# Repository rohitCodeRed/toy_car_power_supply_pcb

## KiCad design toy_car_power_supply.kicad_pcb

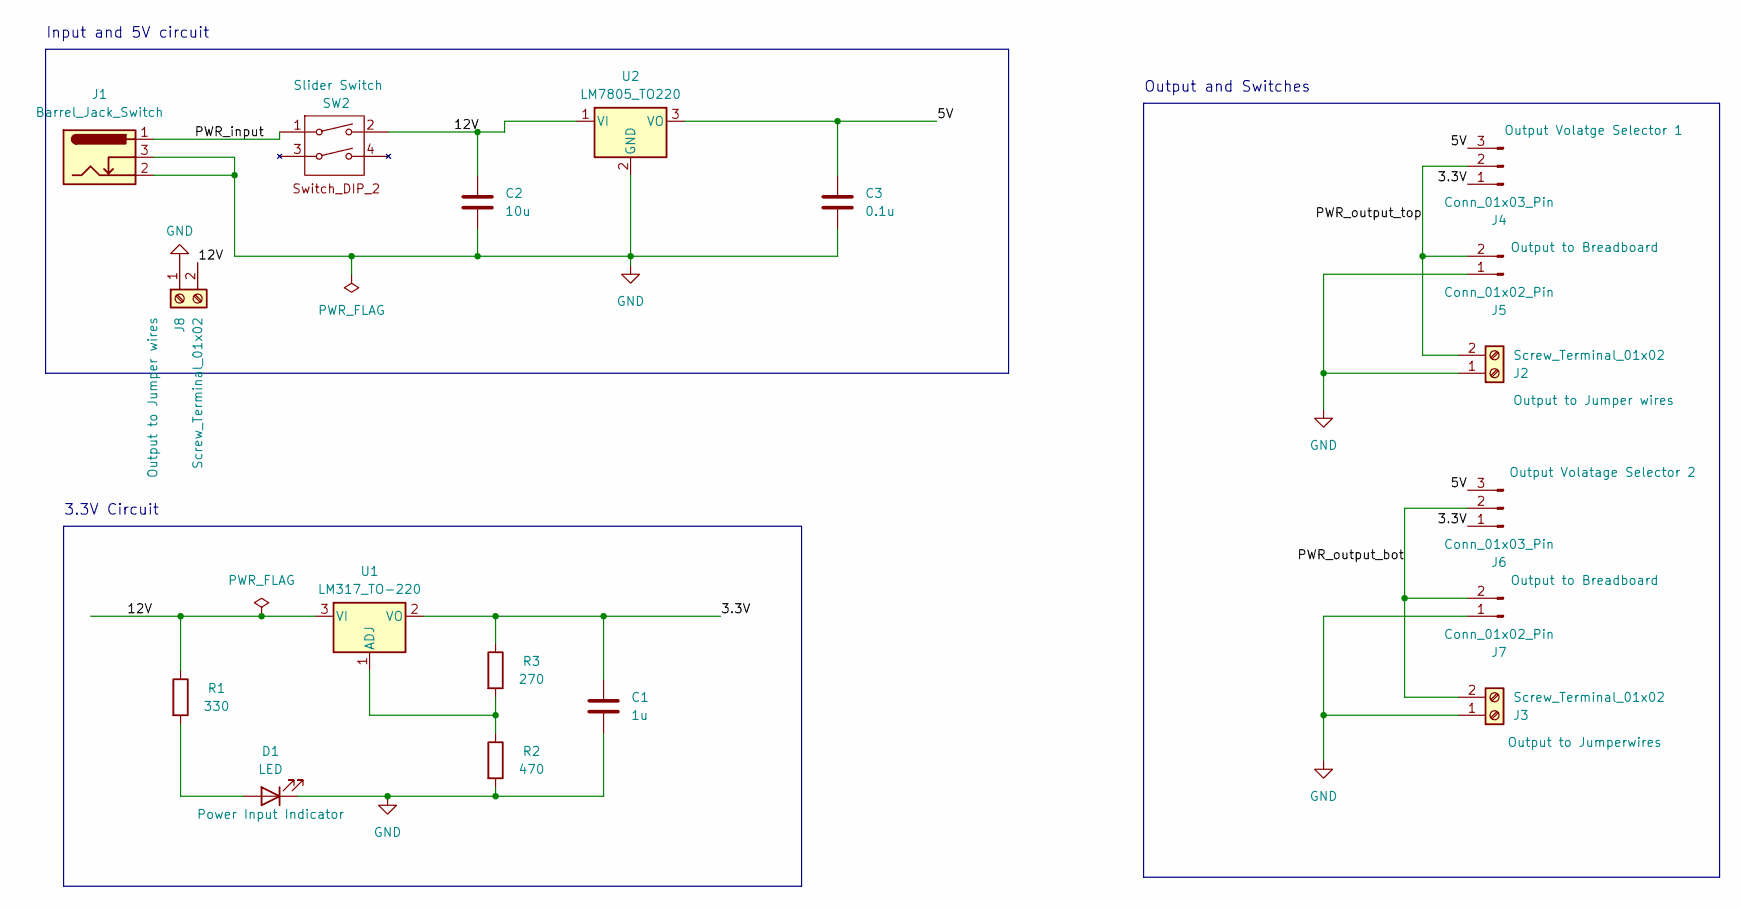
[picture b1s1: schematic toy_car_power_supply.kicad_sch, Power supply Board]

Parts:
C1: 1u; C_Disc_D3.0mm_W1.6mm_P2.50mm
C2: 10u; C_Disc_D3.0mm_W1.6mm_P2.50mm
C3: 0.1u; C_Disc_D3.0mm_W1.6mm_P2.50mm
D1: LED; LED_D5.0mm
J1: Barrel_Jack_Switch; BarrelJack_Horizontal
J2, J3, J8: Screw_Terminal_01x02; TerminalBlock_bornier-2_P5.08mm
J4, J6: Conn_01x03_Pin; PinHeader_1x03_P2.54mm_Vertical
J5, J7: Conn_01x02_Pin; PinHeader_1x02_P2.54mm_Vertical
R1: 330; R_Axial_DIN0204_L3.6mm_D1.6mm_P7.62mm_Horizontal
R2: 470; R_Axial_DIN0204_L3.6mm_D1.6mm_P7.62mm_Horizontal
R3: 270; R_Axial_DIN0204_L3.6mm_D1.6mm_P7.62mm_Horizontal
SW2: Slider Switch; DIP-4_W7.62mm
U1: LM317_TO-220; TO-220-3_Vertical
U2: LM7805_TO220; TO-220-3_Vertical

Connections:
/3.3V: C1.2, J4.1, J6.1, R3.1, U1.2 (VO)
/5V: C3.1, J4.3, J6.3, U2.3 (VO)
/12V: C2.1, J8.2, R1.1, SW2.2, U1.3 (VI), U2.1 (VI)
/PWR_input: J1.1, SW2.1
/PWR_output_bot: J3.2, J6.2, J7.2
/PWR_output_top: J2.2, J4.2, J5.2
GND: C1.1, C2.2, C3.2, D1.1 (K), J1.2, J1.3, J2.1, J3.1, J5.1, J7.1, J8.1, R2.2, U2.2 (GND)
unnamed: D1.2 (A), R1.2
unnamed: R2.1, R3.2, U1.1 (ADJ)

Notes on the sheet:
3.3V Circuit
Output and Switches
Input and 5V circuit

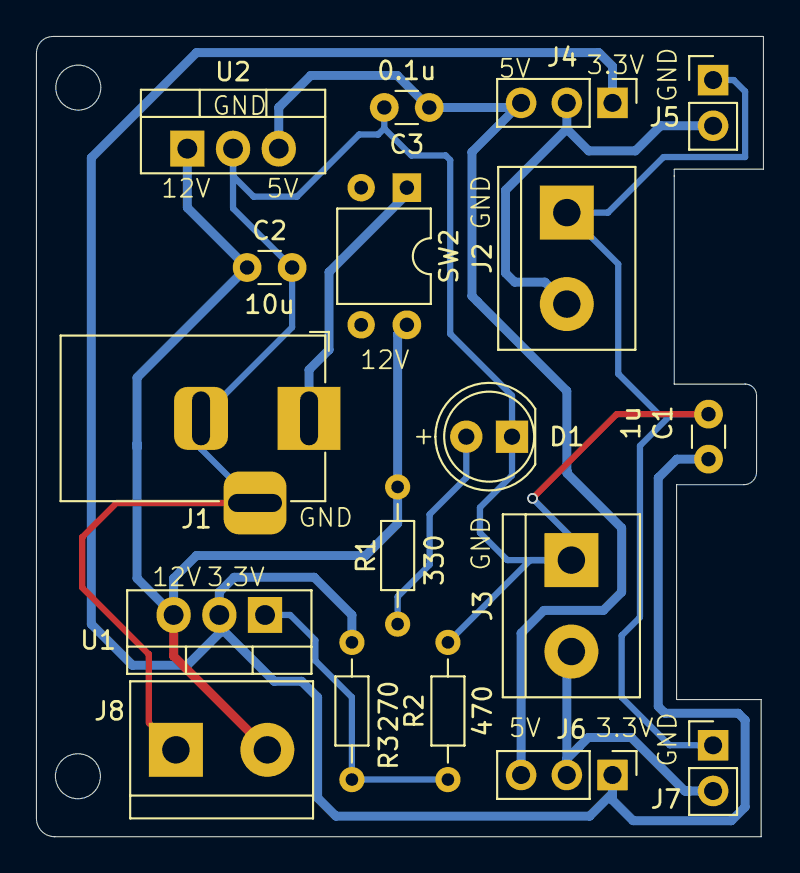
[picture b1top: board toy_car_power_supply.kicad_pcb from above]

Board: 2 copper layers, 40.4 x 44.5 mm, 18 parts (0 on the bottom side), 9 nets.

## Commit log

2024-08-11 Foot print and schema of pcb.
2024-08-11 Changes sheet name
2024-08-13 Updated track width for all tracks
2024-08-14 Updated resistance value r1 = 270 r2 = 470
2024-08-15 Updated with custom switch with 4 pin
2024-08-15 Remove redundant library
2024-08-16 Added conector for 12 v supply
2024-10-18 Updated pcb
2024-10-19 pcb updated
